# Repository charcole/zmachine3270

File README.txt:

ZMachine Interpreter for IBM 3270 compatible terminals
======================================================

Small dongle that provides Z-Machine interpreter (Infocom games), TN3270 (Telnet for 3270), SSH and Wikipedia clients.

Plugs into the serial port and uses SDLC and SNA networking protocols to communicate with the terminal over a 25-pin RS232 port.

Specificly this was designed for an Informer 270 376/SNA terminal.

There's a short video on YouTube at...
https://www.youtube.com/watch?v=U6nj1dibTCA

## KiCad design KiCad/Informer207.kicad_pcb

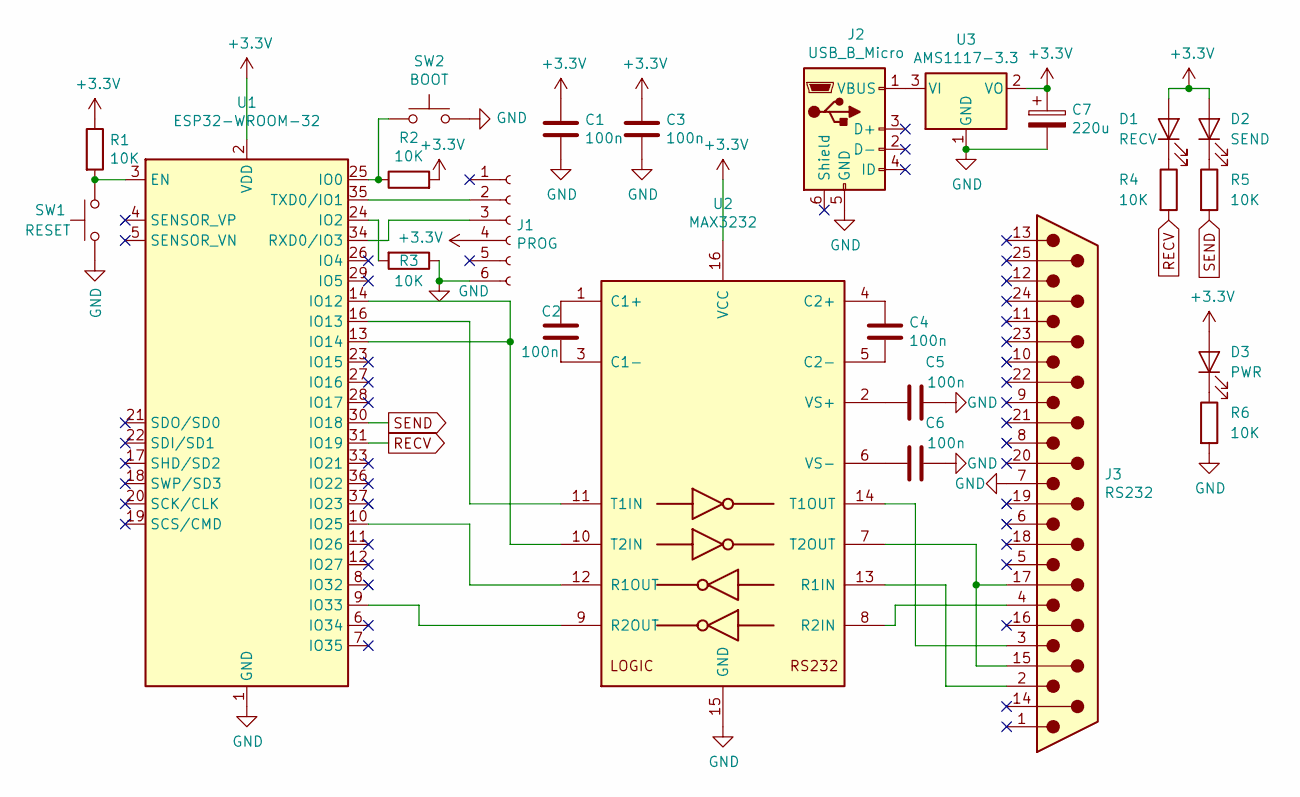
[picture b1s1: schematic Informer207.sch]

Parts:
C1, C2, C3, C4, C5, C6: 100n; C_1206_3216Metric_Pad1.42x1.75mm_HandSolder
C7: 220u; CP_EIA-6032-20_AVX-F_Pad2.25x2.35mm_HandSolder
D1: RECV; LED_1206_3216Metric_Pad1.42x1.75mm_HandSolder
D2: SEND; LED_1206_3216Metric_Pad1.42x1.75mm_HandSolder
D3: PWR; LED_1206_3216Metric_Pad1.42x1.75mm_HandSolder
J1: PROG; PinHeader_1x06_P2.54mm_Vertical
J2: USB_B_Micro; USB_Micro-B_Molex-105017-0001
J3: RS232; DSUB-25_Male_Horizontal_D25P13A4PL00LF
R1, R2, R3, R4, R5, R6: 10K; R_1206_3216Metric_Pad1.42x1.75mm_HandSolder
SW1: RESET; SW_SPST_CK_RS282G05A3
SW2: BOOT; SW_SPST_CK_RS282G05A3
U1: ESP32-WROOM-32
U2: MAX3232; SOIC-16_3.9x9.9mm_P1.27mm
U3: AMS1117-3.3; SOT-223-3_TabPin2

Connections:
+3V3: C1.1, C3.1, C7.1, D1.2 (A), D2.2 (A), D3.2 (A), J1.4, R1.1, R2.2, U1.2 (VDD), U2.16 (VCC), U3.2 (VO)
GND: C1.2, C3.2, C5.2, C6.2, C7.2, J1.6, J2.5 (GND), J3.7, R3.1, R6.2, SW1.1, SW2.2, U1.1 (GND), U1.15 (GND), U1.38 (GND), U2.15 (GND), U3.1 (GND)
unnamed: C2.1, U2.1 (C1+)
unnamed: C2.2, U2.3 (C1-)
unnamed: C4.1, U2.4 (C2+)
unnamed: C4.2, U2.5 (C2-)
unnamed: C5.1, U2.2 (VS+)
unnamed: C6.1, U2.6 (VS-)
unnamed: D1.1 (K), R4.1
unnamed: D2.1 (K), R5.1
unnamed: D3.1 (K), R6.1
unnamed: J1.2, U1.35 (TXD0/IO1)
unnamed: J1.3, U1.34 (RXD0/IO3)
unnamed: J2.1 (VBUS), U3.3 (VI)
unnamed: J3.2, U2.13 (R1IN)
unnamed: J3.3, U2.14 (T1OUT)
unnamed: J3.4, U2.8 (R2IN)
unnamed: J3.15, J3.17, U2.7 (T2OUT)
unnamed: R1.2, SW1.2, U1.3 (EN)
unnamed: R2.1, SW2.1, U1.25 (IO0)
unnamed: R3.2, U1.24 (IO2)
unnamed: U1.9 (IO33), U2.9 (R2OUT)
unnamed: U1.10 (IO25), U2.12 (R1OUT)
unnamed: U1.13 (IO14), U1.14 (IO12), U2.10 (T2IN)
unnamed: U1.16 (IO13), U2.11 (T1IN)
RECV: R4.2, U1.31 (IO19)
SEND: R5.2, U1.30 (IO18)

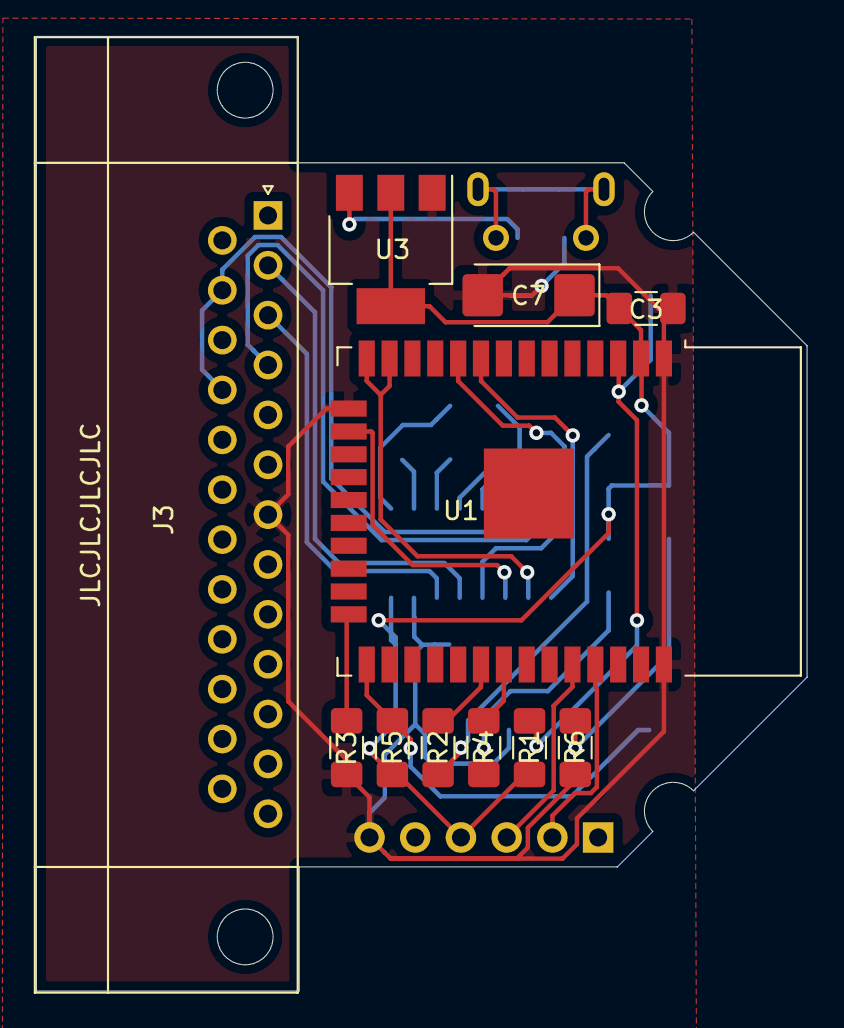
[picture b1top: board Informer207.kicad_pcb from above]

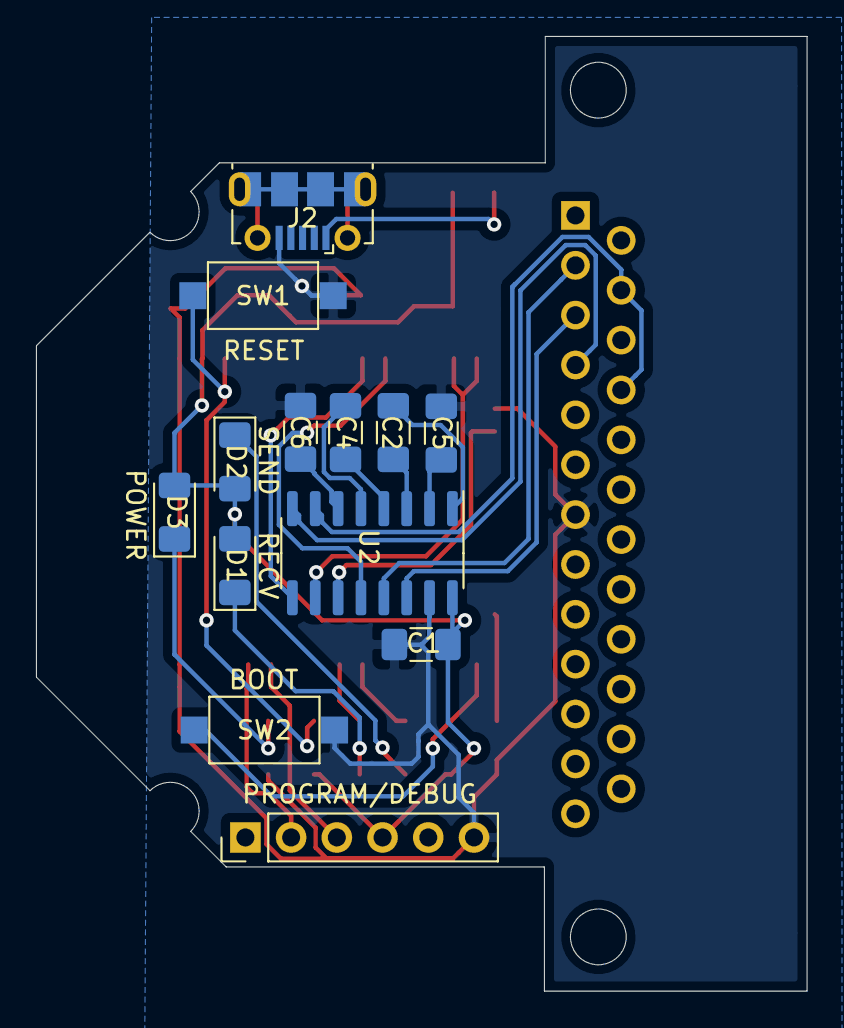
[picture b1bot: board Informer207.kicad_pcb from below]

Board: 2 copper layers, 42.8 x 53.0 mm, 24 parts (13 on the bottom side), 27 nets.

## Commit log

2020-06-10 ESP32 program template (simplified version of train clock)
2020-06-14 Clockless serial
2020-06-14 First signs of life
2020-06-19 First successful send and recieve
2020-06-20 First successful message displayed on screen
2020-06-20 Started organizing project better
2020-06-20 Add build task
2020-06-20 Hide build files
2020-06-20 Moved all 3270 related code out of main
2020-06-20 More reorganization
2020-06-20 Split out packet processing
2020-06-20 Two way text
2020-06-20 Remove pointless waits
2020-06-20 Ask for packet again if invalid
2020-06-20 Include zops (Z-machine)
2020-06-20 Game data and reduced callstack data
2020-06-21 Reduced zops memory footprint
2020-06-21 Working zmachine player!
2020-06-21 Echo back input
2020-06-21 Avoid VSCode flagging spurious problems
2020-06-23 More reliable recieve and sped up send
2020-06-23 Up baud rate and deal with out of sequence packets
2020-06-25 Verified correct SPI mode / edge trigger
2020-06-27 First pass PCB design
2020-06-27 Added possible Ready To Recieve line (some activity on it)
2020-06-27 PCB order gerbers
2020-06-28 Status line and compressed screens
2020-06-28 Added word wrap
2020-06-28 Save and restore (untested)
2020-06-28 Fixes for saving/restoring
2020-06-30 Arbitarily sized save files
2020-06-30 Remove binary
2020-07-01 Ask user for file name when saving
2020-07-01 Game from partition
2020-07-02 Make multiple games available
2020-07-03 Chaining and flow control
2020-07-04 Very basic TN3270 support
2020-07-05 More refined TN3270 implementation
2020-07-12 Very simplistic Wikipedia browser
2020-07-12 Basic SSH implementation (using libSSH2)
2020-07-13 Hide password when logging in via SSH
2020-07-15 Reduce SSH memory usage (had broken Wiki)
2020-07-15 Remove embedded game
2020-07-15 Small tweaks to improve experience
2020-07-16 Interactive SSH shell
2020-07-18 Preserve status line when scrolling
2020-07-18 3D printed case for PCB
2020-07-29 ZMachine version 4, 5 and 8 support
2020-07-29 Fix for Trinity crash, out of range mem stream
2020-07-30 Missing input from version 4+ integrate
2020-08-01 Tweaked new screen model for terminal
2020-08-01 Z-machine cursors aren't zero indexed
2020-08-01 Extended mappings (sadly no square brackets)
2020-08-01 Add secret fourth game for testing bigger games
2020-08-02 Change game selection
2020-08-02 Hacked in better single character reading
2020-08-05 print_addr and random sign fixes
2020-08-05 Prompt if displaying too many lines for screen
2020-08-07 Changed EBCDIC mapping to match terminal
2020-08-24 Small fix to MORE prompt (doesn't lose wordwrap)
2020-08-24 Added comment explaining unusual style
2020-08-24 Added readme and license
2020-08-25 Add firmware ROMs
2020-08-25 Add Informer 207 emulator built on MAME
2020-09-01 Added way of updating game datawe over WiFi
2020-09-09 Improved char gen ROM dump
2020-09-09 Add the PCB designators
2020-09-12 Redumped 79590-023 ROM as checksum didn't match label
2020-09-13 Experimental SoftDongle: Fully software version of dongle for use with MAME
